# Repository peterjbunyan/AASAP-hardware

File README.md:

# AASAP-hardware
KiCAD Schematics, PCBs and Gerbers for the AASAP computer's hardware.

The AASAP (Almost As Simple As Possible) computer is loosely based on the [8 bit breadboard computer](https://eater.net/8bit) built by Ben Eater which is turn was based on the SAP-1 (Simple As Possible - 1) design. The design of this computer builds on the knowledge from [Ben Eater's YouTube videos](https://www.youtube.com/playlist?list=PLowKtXNTBypGqImE405J2565dvjafglHU) but does not directly copy the design, and differs in a number of areas, the key ones being:

- Moving to a 16 bit address system for the internal RAM and the Program Counter.
- 32KB of RAM for program and data storage.
- 22 Control Bits to control input, output and special functions for each modules.
- A Wait line to halt the clock while waiting for external input.
- A Program line to disable the output of the control bits, allowing for external manual or automated writing of program data to RAM.
- Output to a 16x4 Character LCD.
- A modular PCB design based on individual cards that are linked together on a backplane PCB.

Here you can see the almost complete AASAP running the following code to count down from 4 to zero:

    start:
      LDI 4     ; Load the A Register with an immediate value (4)
    loop:
      SUI 1     ; Subtract the immediate value (1) from the A Register
      JNZ loop  ; If the result was not zero, jump to loop
      JMP       ; Jump to start

The board connected at the top of the image is a bootloader based on an Arduino Nano. It can write to and read from RAM, and provides a clock for the AASAP.

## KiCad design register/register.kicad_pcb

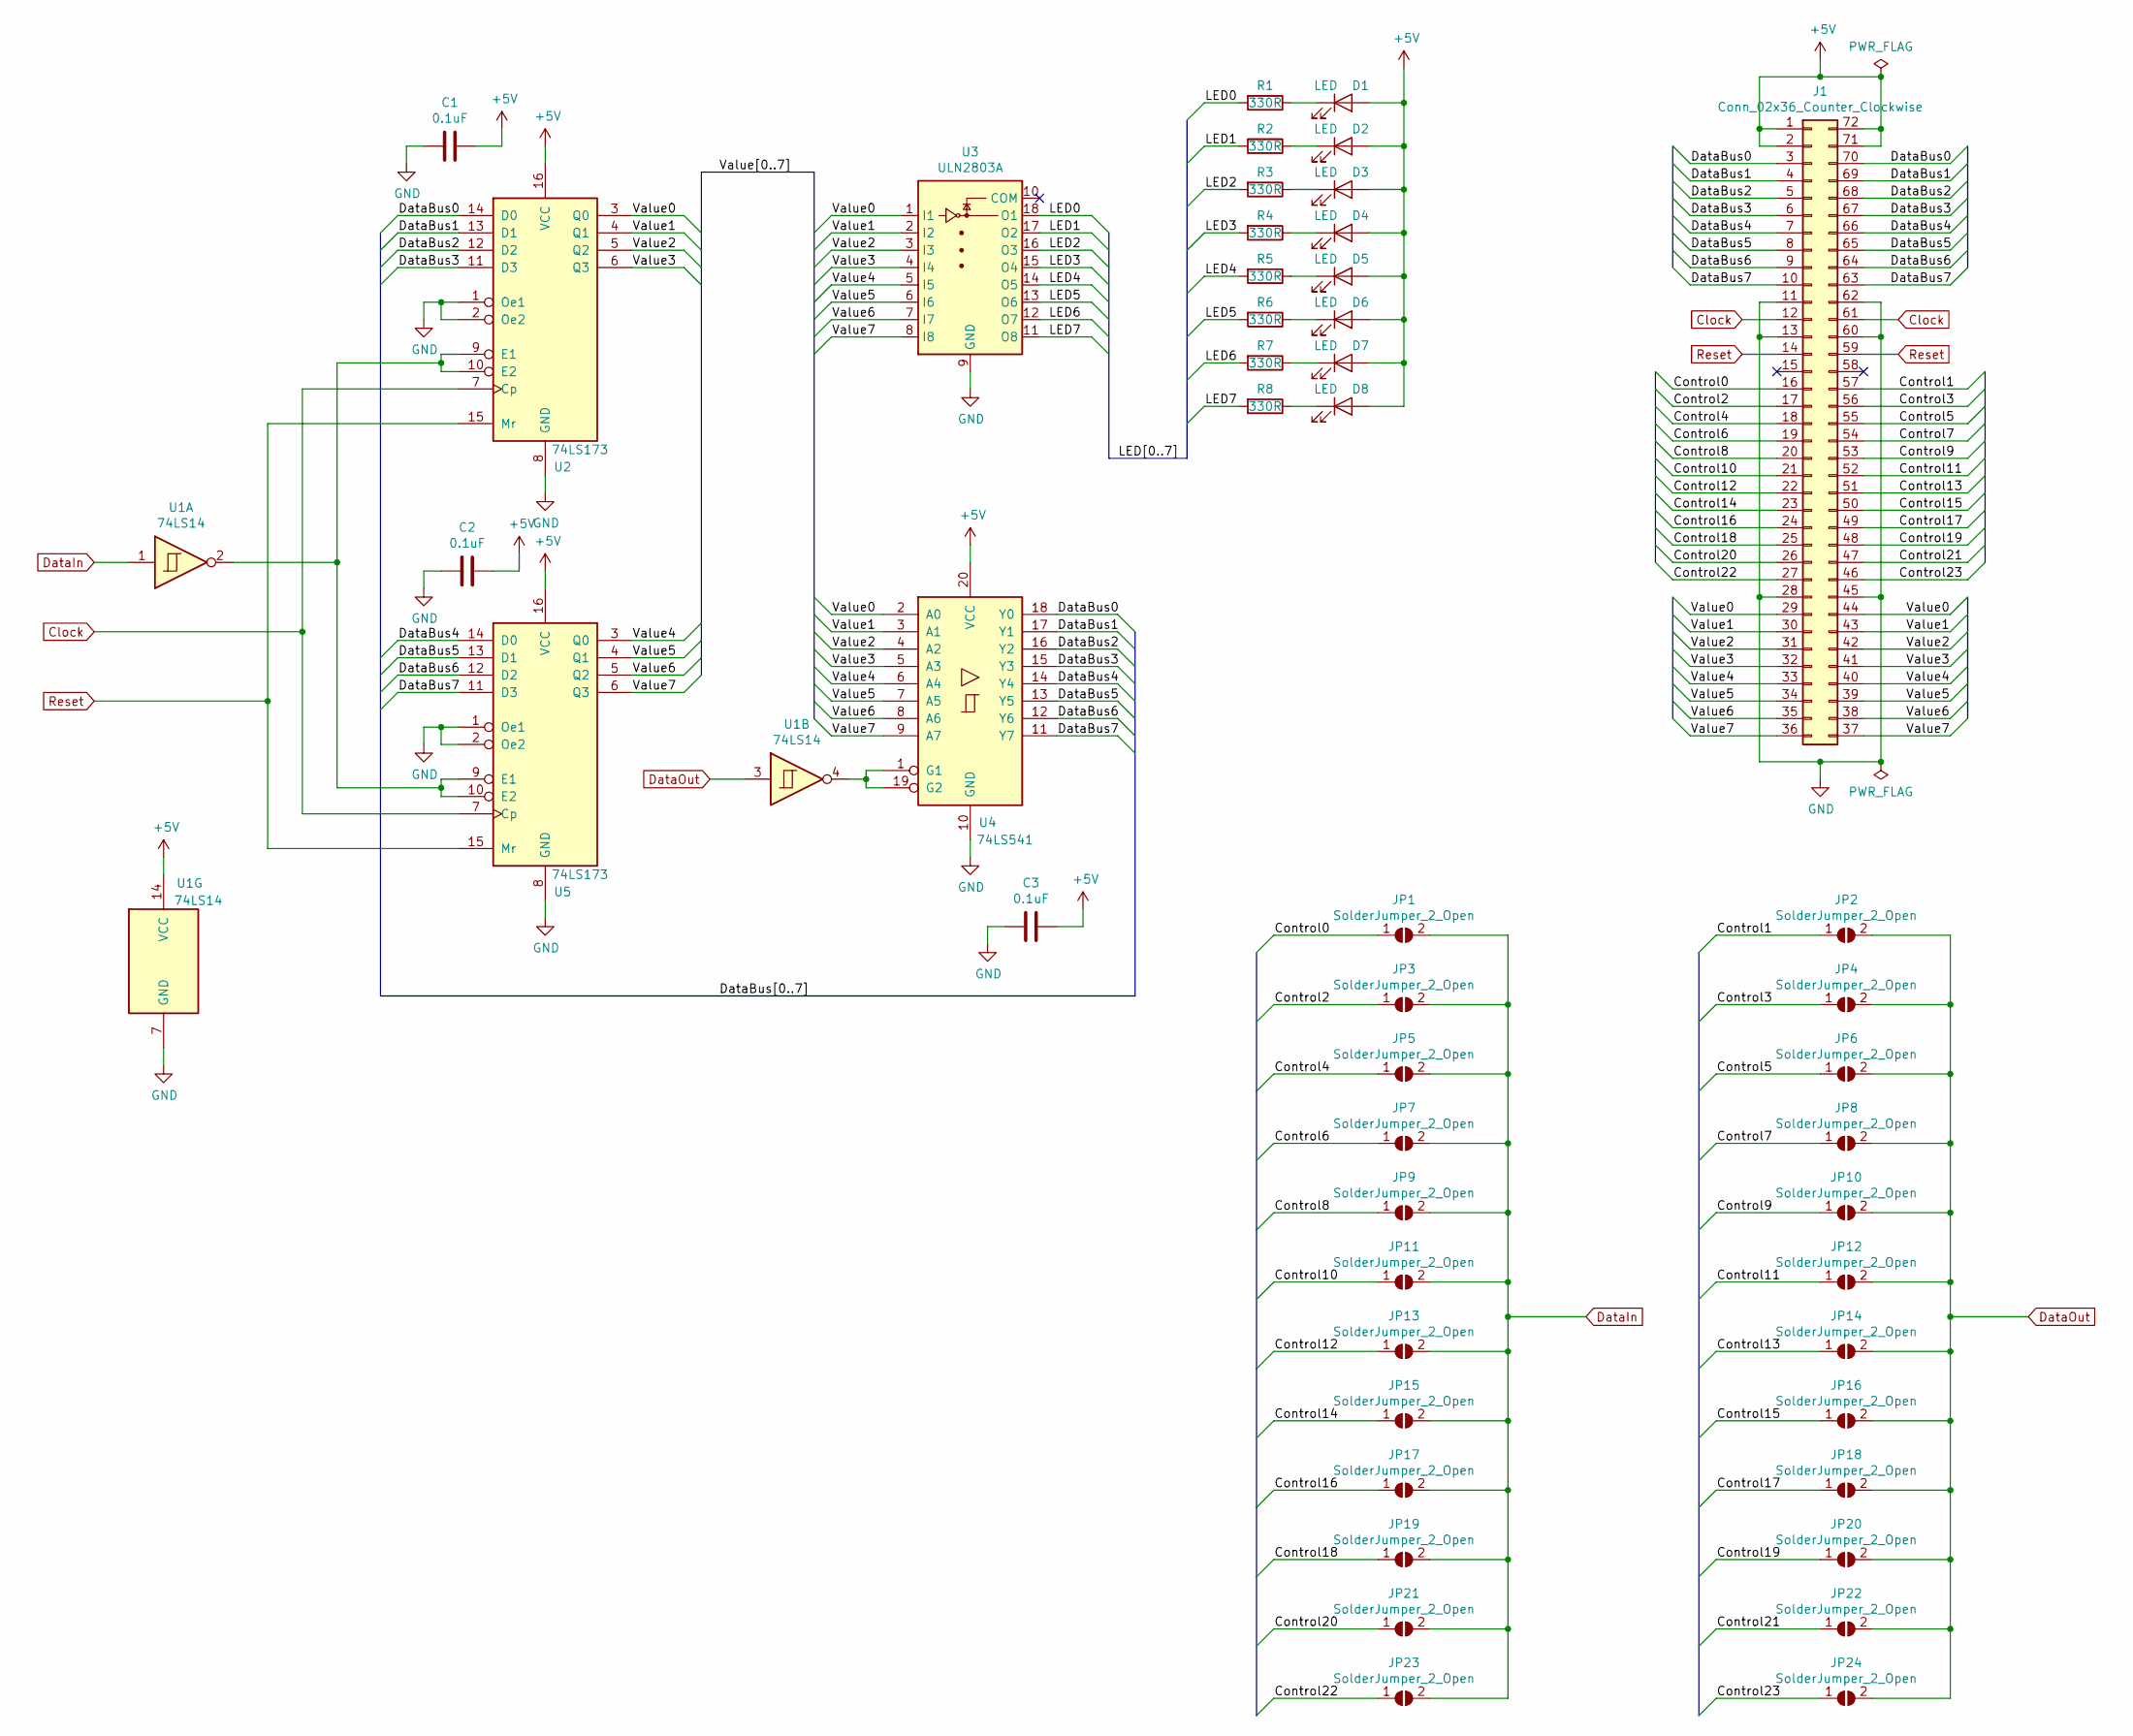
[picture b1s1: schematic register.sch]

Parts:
C1, C2, C3: 0.1uF; C_Disc_D6.0mm_W2.5mm_P5.00mm
D1, D2, D3, D4, D5, D6, D7, D8: LED; LED_D5.0mm_Horizontal_O1.27mm_Z3.0mm
J1: Conn_02x36_Counter_Clockwise; Standard_Edge_II_72_POS_PCB
JP1, JP2, JP3, JP4, JP5, JP6, JP7, JP8, JP9, JP10, JP11, JP12, JP13, JP14, JP15, JP16, JP17, JP18, JP19, JP20, JP21, JP22, JP23, JP24: SolderJumper_2_Open; SolderJumper-2_P1.3mm_Open_TrianglePad1.0x1.5mm
R1, R2, R3, R4, R5, R6, R7, R8: 330R; R_Axial_DIN0204_L3.6mm_D1.6mm_P7.62mm_Horizontal
U1: 74LS14; DIP-14_W7.62mm_Socket
U2, U5: 74LS173; DIP-16_W7.62mm_Socket
U3: ULN2803A; DIP-18_W7.62mm_Socket
U4: 74LS541; DIP-20_W7.62mm_Socket

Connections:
+5V: C1.1, C2.1, C3.1, D1.2 (A), D2.2 (A), D3.2 (A), D4.2 (A), D5.2 (A), D6.2 (A), D7.2 (A), D8.2 (A), J1.1, J1.2, J1.71, J1.72, U1.14 (VCC), U2.16 (VCC), U4.20 (VCC), U5.16 (VCC)
/Control0: J1.16, JP1.1 (A)
/Control1: J1.57, JP2.1 (A)
/Control2: J1.17, JP3.1 (A)
/Control3: J1.56, JP4.1 (A)
/Control4: J1.18, JP5.1 (A)
/Control5: J1.55, JP6.1 (A)
/Control6: J1.19, JP7.1 (A)
/Control7: J1.54, JP8.1 (A)
/Control8: J1.20, JP9.1 (A)
/Control9: J1.53, JP10.1 (A)
/Control10: J1.21, JP11.1 (A)
/Control11: J1.52, JP12.1 (A)
/Control12: J1.22, JP13.1 (A)
/Control13: J1.51, JP14.1 (A)
/Control14: J1.23, JP15.1 (A)
/Control15: J1.50, JP16.1 (A)
/Control16: J1.24, JP17.1 (A)
/Control17: J1.49, JP18.1 (A)
/Control18: J1.25, JP19.1 (A)
/Control19: J1.48, JP20.1 (A)
/Control20: J1.26, JP21.1 (A)
/Control21: J1.47, JP22.1 (A)
/Control22: J1.27, JP23.1 (A)
/Control23: J1.46, JP24.1 (A)
/DataBus0: J1.3, J1.70, U2.14 (D0), U4.18 (Y0)
/DataBus1: J1.4, J1.69, U2.13 (D1), U4.17 (Y1)
/DataBus2: J1.5, J1.68, U2.12 (D2), U4.16 (Y2)
/DataBus3: J1.6, J1.67, U2.11 (D3), U4.15 (Y3)
/DataBus4: J1.7, J1.66, U4.14 (Y4), U5.14 (D0)
/DataBus5: J1.8, J1.65, U4.13 (Y5), U5.13 (D1)
/DataBus6: J1.9, J1.64, U4.12 (Y6), U5.12 (D2)
/DataBus7: J1.10, J1.63, U4.11 (Y7), U5.11 (D3)
/LED0: R1.2, U3.18 (O1)
/LED1: R2.2, U3.17 (O2)
/LED2: R3.2, U3.16 (O3)
/LED3: R4.2, U3.15 (O4)
/LED4: R5.2, U3.14 (O5)
/LED5: R6.2, U3.13 (O6)
/LED6: R7.2, U3.12 (O7)
/LED7: R8.2, U3.11 (O8)
/Value0: J1.29, J1.44, U2.3 (Q0), U3.1 (I1), U4.2 (A0)
/Value1: J1.30, J1.43, U2.4 (Q1), U3.2 (I2), U4.3 (A1)
/Value2: J1.31, J1.42, U2.5 (Q2), U3.3 (I3), U4.4 (A2)
/Value3: J1.32, J1.41, U2.6 (Q3), U3.4 (I4), U4.5 (A3)
/Value4: J1.33, J1.40, U3.5 (I5), U4.6 (A4), U5.3 (Q0)
/Value5: J1.34, J1.39, U3.6 (I6), U4.7 (A5), U5.4 (Q1)
/Value6: J1.35, J1.38, U3.7 (I7), U4.8 (A6), U5.5 (Q2)
/Value7: J1.36, J1.37, U3.8 (I8), U4.9 (A7), U5.6 (Q3)
Clock: J1.12, J1.61, U2.7 (Cp), U5.7 (Cp)
DataIn: JP1.2 (B), JP3.2 (B), JP5.2 (B), JP7.2 (B), JP9.2 (B), JP11.2 (B), JP13.2 (B), JP15.2 (B), JP17.2 (B), JP19.2 (B), JP21.2 (B), JP23.2 (B), U1.1
DataOut: JP2.2 (B), JP4.2 (B), JP6.2 (B), JP8.2 (B), JP10.2 (B), JP12.2 (B), JP14.2 (B), JP16.2 (B), JP18.2 (B), JP20.2 (B), JP22.2 (B), JP24.2 (B), U1.3
GND: C1.2, C2.2, C3.2, J1.11, J1.13, J1.28, J1.45, J1.60, J1.62, U1.7 (GND), U2.1 (Oe1), U2.2 (Oe2), U2.8 (GND), U3.9 (GND), U4.10 (GND), U5.1 (Oe1), U5.2 (Oe2), U5.8 (GND)
unnamed: D1.1 (K), R1.1
unnamed: D2.1 (K), R2.1
unnamed: D3.1 (K), R3.1
unnamed: D4.1 (K), R4.1
unnamed: D5.1 (K), R5.1
unnamed: D6.1 (K), R6.1
unnamed: D7.1 (K), R7.1
unnamed: D8.1 (K), R8.1
unnamed: U1.2, U2.9 (E1), U2.10 (E2), U5.9 (E1), U5.10 (E2)
unnamed: U1.4, U4.1 (G1), U4.19 (G2)
Reset: J1.14, J1.59, U2.15 (Mr), U5.15 (Mr)

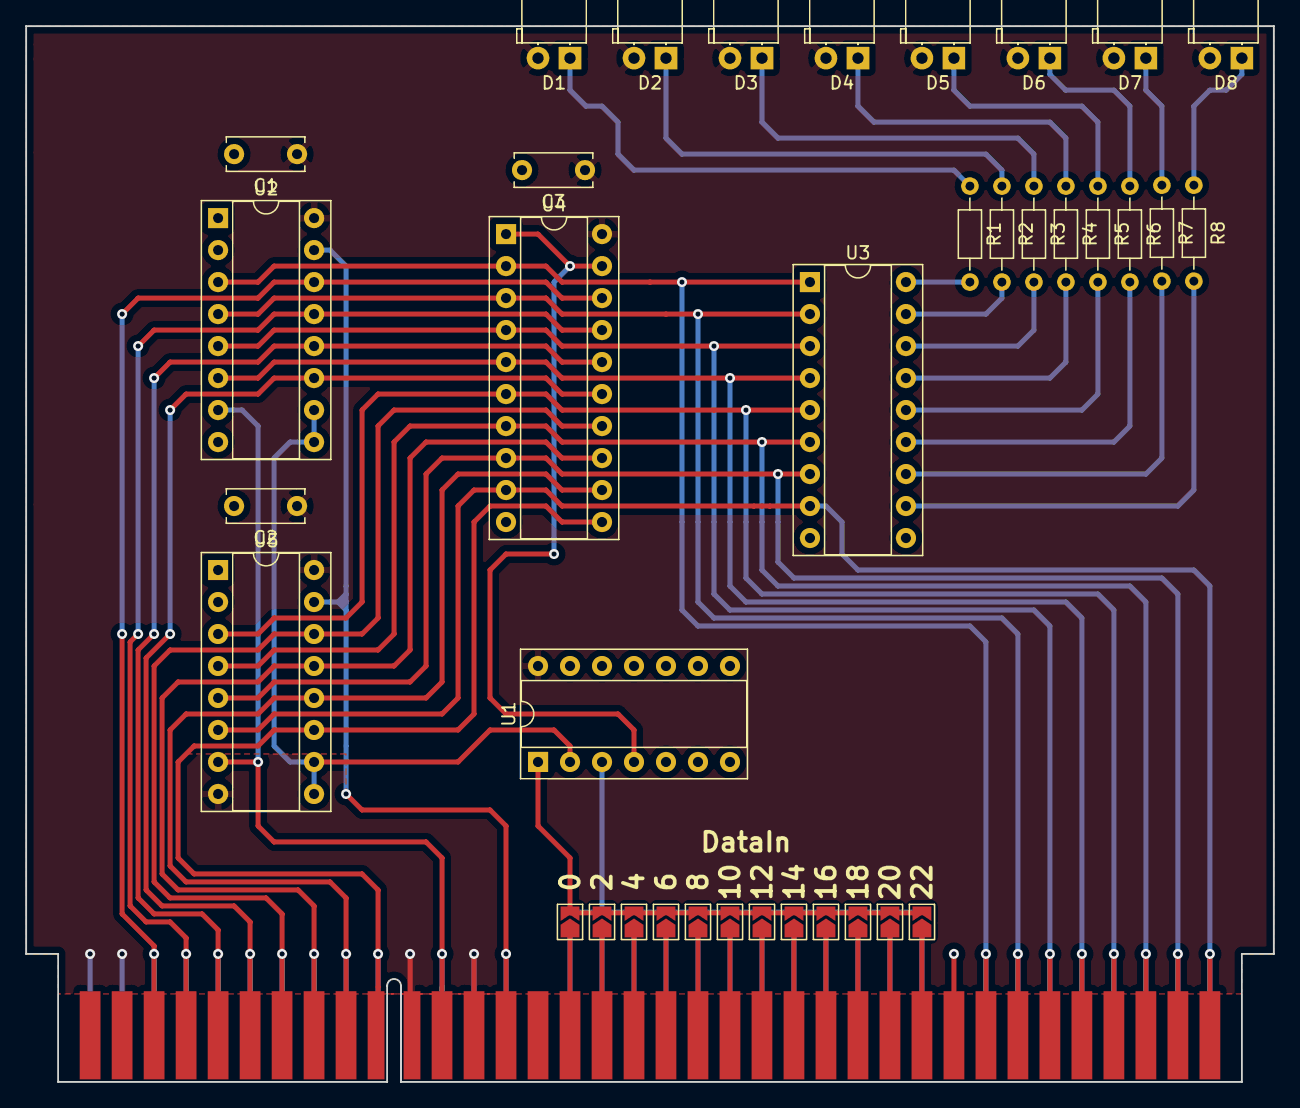
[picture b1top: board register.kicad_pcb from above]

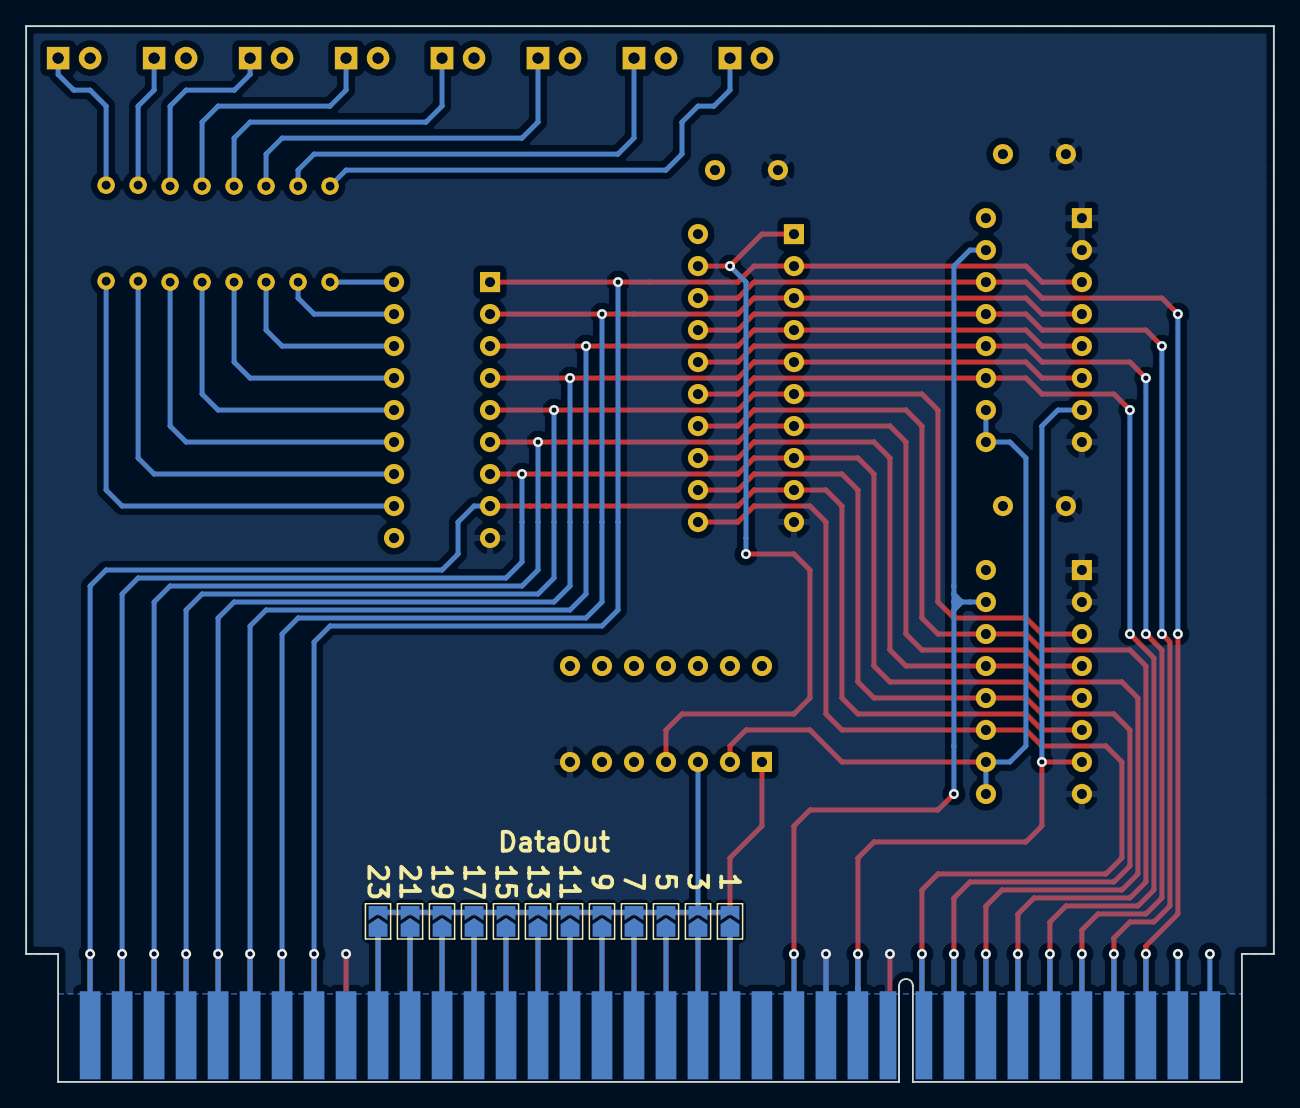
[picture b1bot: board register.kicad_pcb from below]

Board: 2 copper layers, 99.1 x 83.8 mm, 49 parts (12 on the bottom side), 64 nets.

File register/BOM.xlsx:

| Manufacturer | MPN | Description | Value | Quantity | Part references
 | ST Microelectronics | ULN2803A | Darlington Transistor Arrays, DIP18 |  | 1
 | Multicomp Pro | MCL053PD | 5mm Light emitting diode - Red |  | 8
 | Multicomp Pro | 9339418 | 1/4W Through Hole Resistor | 330R | 8
 | Texas Instruments | SN74LS14N | Hex Inverter |  | 1
 | Texas Instruments | SN74LS541N | Buffer |  | 1
 | Texas Instruments | SN74LS173AN | 4-bit D-type Register, 3 state out |  | 2
 | Multicomp Pro | MCFYU6104Z6 | Ceramic Capacitor | 0.1uF | 4
 | Amphenol ICC | DILB20P-223TLF | 20 Pin DIP Socket - 7.62mm |  | 1
 | Amphenol ICC | DILB18P223TLF | 18 Pin DIP Socket - 7.62mm |  | 1
 | Amphenol ICC | DILB16P223TLF | 16 Pin DIP Socket - 7.62mm |  | 2
 | Amphenol ICC | DILB14P-223TLF | 14 Pin DIP Socket - 7.62mm |  | 1

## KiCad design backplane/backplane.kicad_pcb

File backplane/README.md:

# AASAP backplane
This PCB is the backplane that connects all of the computers modules together. It can be chained to other modules using IDC cables, which is necessary to add the number of module required for the computer to function

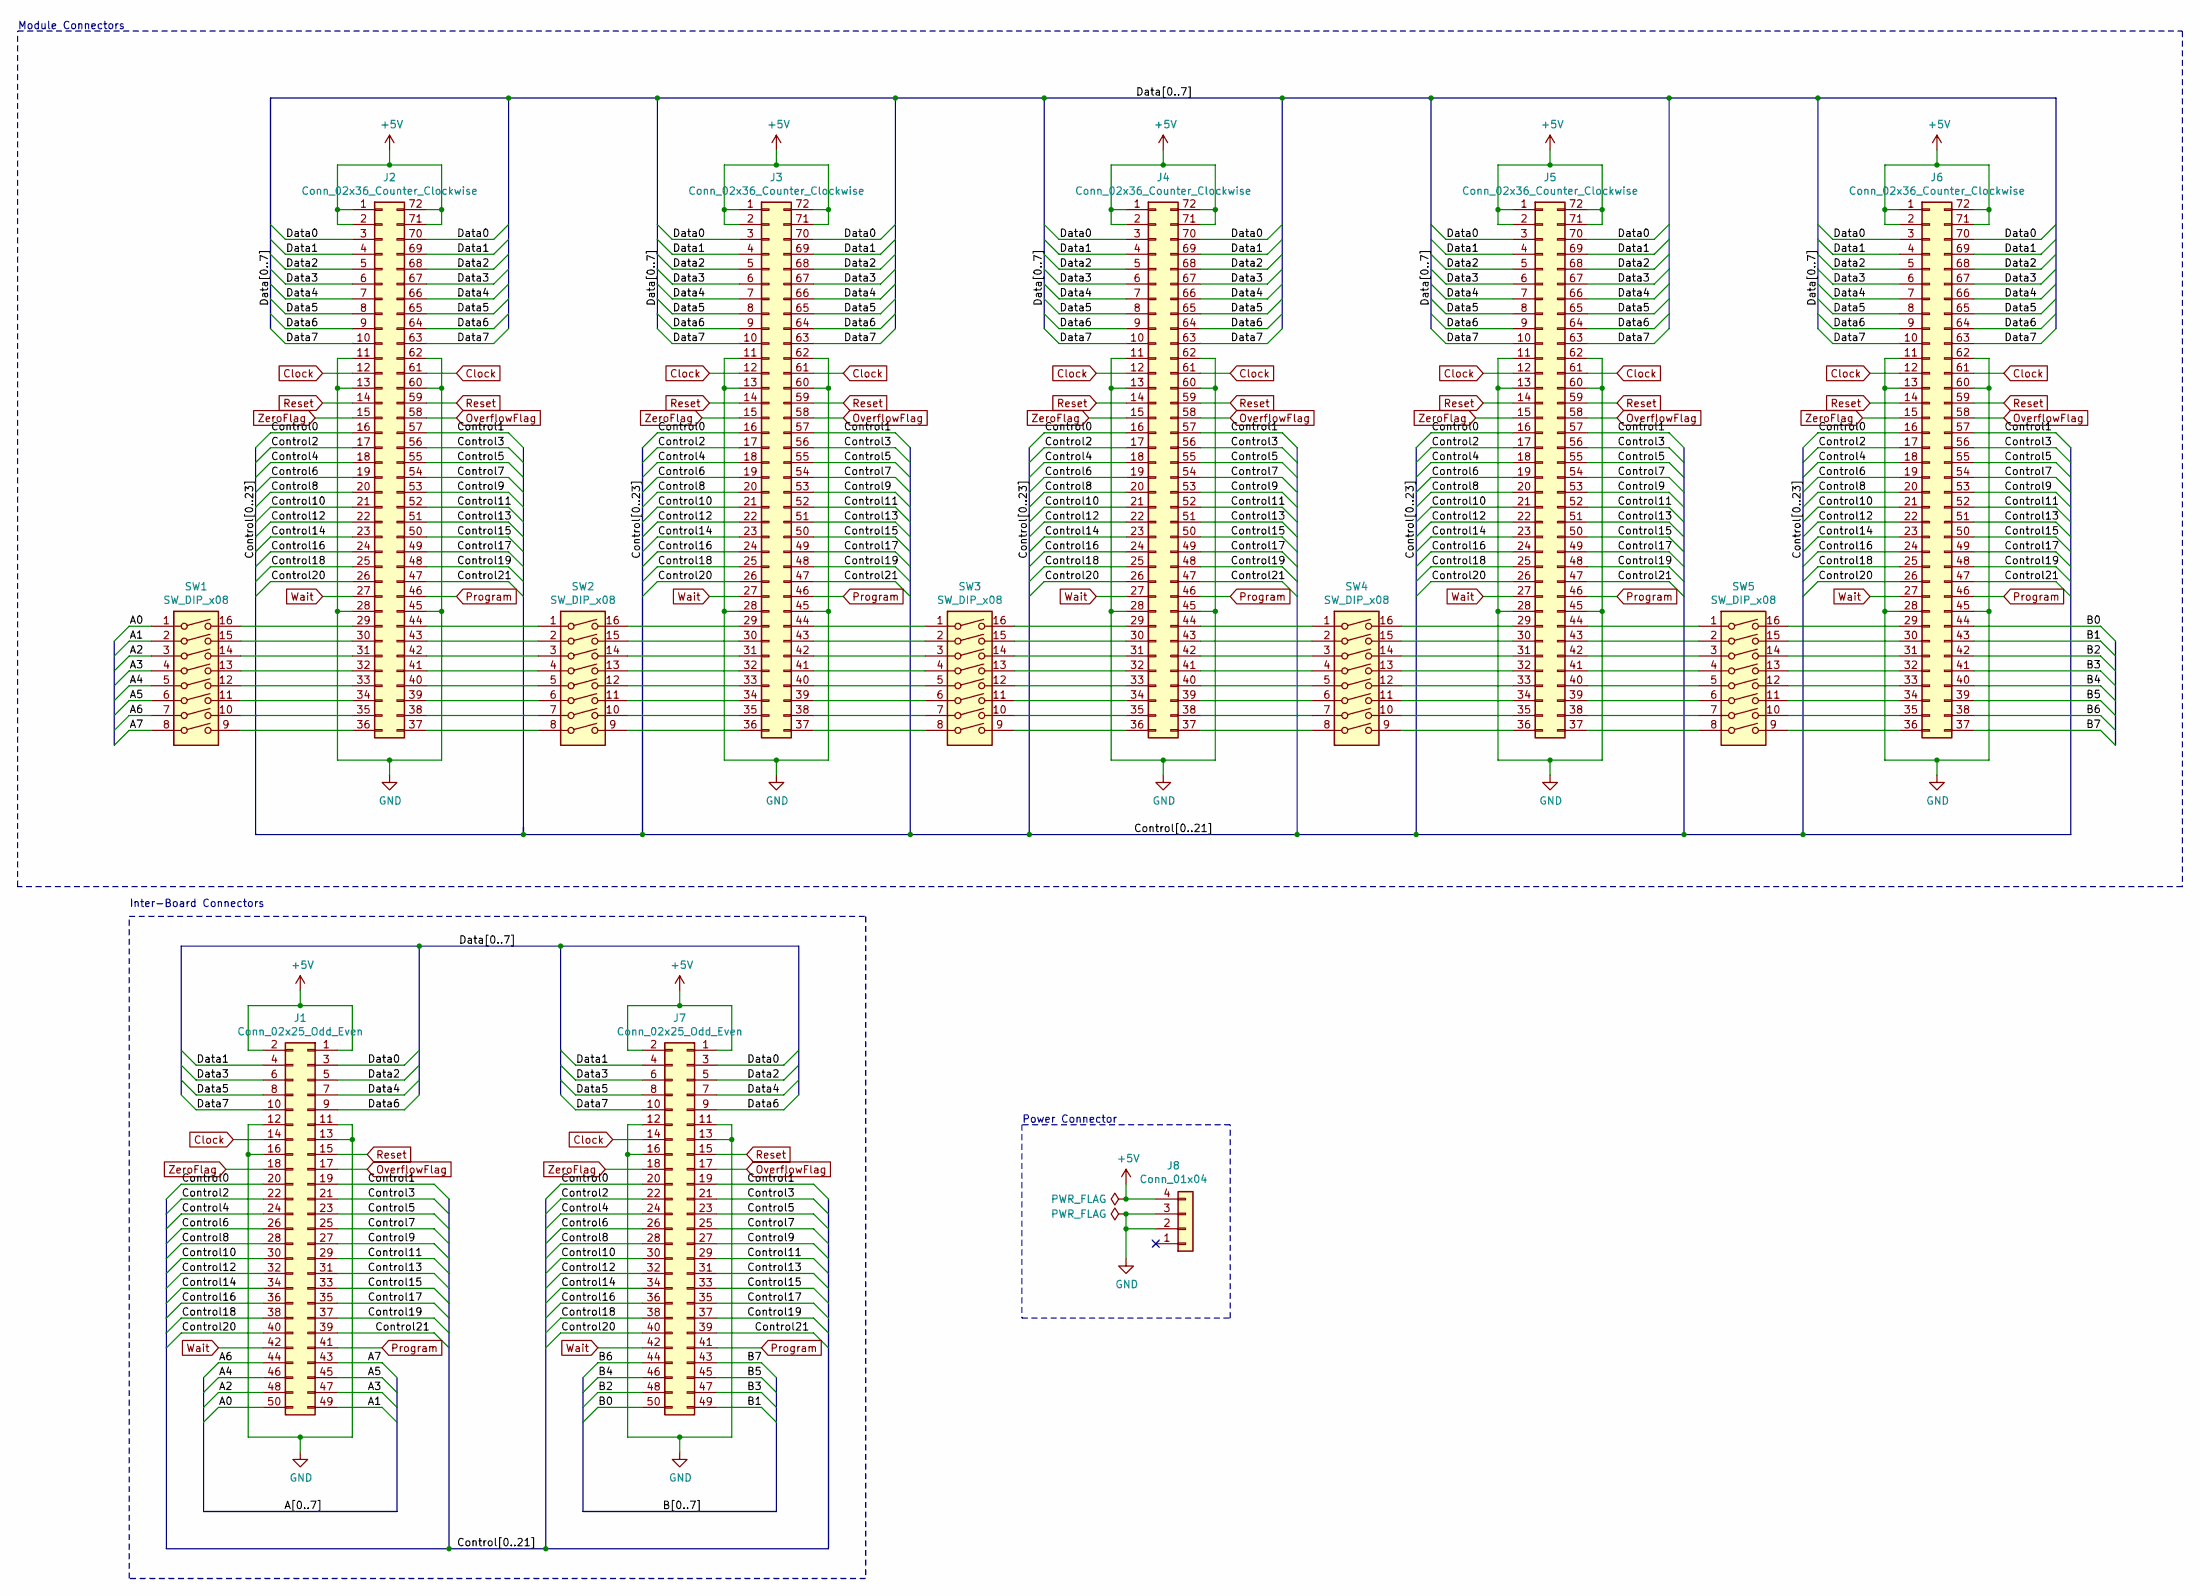
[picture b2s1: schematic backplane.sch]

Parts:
J1, J7: Conn_02x25_Odd_Even; Multicomp_MC9A12-5034_2x25_P2.54mm_Vertical
J2, J3, J4, J5, J6: Conn_02x36_Counter_Clockwise; Standard_Edge_II_72_POS
J8: Conn_01x04; TerminalBlock_bornier-4_P5.08mm
SW1, SW2, SW3, SW4, SW5: SW_DIP_x08; SW_DIP_SPSTx08_Slide_9.78x22.5mm_W7.62mm_P2.54mm

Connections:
+5V: J1.1, J1.2, J2.1, J2.2, J2.71, J2.72, J3.1, J3.2, J3.71, J3.72, J4.1, J4.2, J4.71, J4.72, J5.1, J5.2, J5.71, J5.72, J6.1, J6.2, J6.71, J6.72, J7.1, J7.2, J8.4
/A0: J1.50, SW1.1
/A1: J1.49, SW1.2
/A2: J1.48, SW1.3
/A3: J1.47, SW1.4
/A4: J1.46, SW1.5
/A5: J1.45, SW1.6
/A6: J1.44, SW1.7
/A7: J1.43, SW1.8
/B0: J6.44, J7.50
/B1: J6.43, J7.49
/B2: J6.42, J7.48
/B3: J6.41, J7.47
/B4: J6.40, J7.46
/B5: J6.39, J7.45
/B6: J6.38, J7.44
/B7: J6.37, J7.43
/Control0: J1.20, J2.16, J3.16, J4.16, J5.16, J6.16, J7.20
/Control1: J1.19, J2.57, J3.57, J4.57, J5.57, J6.57, J7.19
/Control2: J1.22, J2.17, J3.17, J4.17, J5.17, J6.17, J7.22
/Control3: J1.21, J2.56, J3.56, J4.56, J5.56, J6.56, J7.21
/Control4: J1.24, J2.18, J3.18, J4.18, J5.18, J6.18, J7.24
/Control5: J1.23, J2.55, J3.55, J4.55, J5.55, J6.55, J7.23
/Control6: J1.26, J2.19, J3.19, J4.19, J5.19, J6.19, J7.26
/Control7: J1.25, J2.54, J3.54, J4.54, J5.54, J6.54, J7.25
/Control8: J1.28, J2.20, J3.20, J4.20, J5.20, J6.20, J7.28
/Control9: J1.27, J2.53, J3.53, J4.53, J5.53, J6.53, J7.27
/Control10: J1.30, J2.21, J3.21, J4.21, J5.21, J6.21, J7.30
/Control11: J1.29, J2.52, J3.52, J4.52, J5.52, J6.52, J7.29
/Control12: J1.32, J2.22, J3.22, J4.22, J5.22, J6.22, J7.32
/Control13: J1.31, J2.51, J3.51, J4.51, J5.51, J6.51, J7.31
/Control14: J1.34, J2.23, J3.23, J4.23, J5.23, J6.23, J7.34
/Control15: J1.33, J2.50, J3.50, J4.50, J5.50, J6.50, J7.33
/Control16: J1.36, J2.24, J3.24, J4.24, J5.24, J6.24, J7.36
/Control17: J1.35, J2.49, J3.49, J4.49, J5.49, J6.49, J7.35
/Control18: J1.38, J2.25, J3.25, J4.25, J5.25, J6.25, J7.38
/Control19: J1.37, J2.48, J3.48, J4.48, J5.48, J6.48, J7.37
/Control20: J1.40, J2.26, J3.26, J4.26, J5.26, J6.26, J7.40
/Control21: J1.39, J2.47, J3.47, J4.47, J5.47, J6.47, J7.39
/Data0: J1.3, J2.3, J2.70, J3.3, J3.70, J4.3, J4.70, J5.3, J5.70, J6.3, J6.70, J7.3
/Data1: J1.4, J2.4, J2.69, J3.4, J3.69, J4.4, J4.69, J5.4, J5.69, J6.4, J6.69, J7.4
/Data2: J1.5, J2.5, J2.68, J3.5, J3.68, J4.5, J4.68, J5.5, J5.68, J6.5, J6.68, J7.5
/Data3: J1.6, J2.6, J2.67, J3.6, J3.67, J4.6, J4.67, J5.6, J5.67, J6.6, J6.67, J7.6
/Data4: J1.7, J2.7, J2.66, J3.7, J3.66, J4.7, J4.66, J5.7, J5.66, J6.7, J6.66, J7.7
/Data5: J1.8, J2.8, J2.65, J3.8, J3.65, J4.8, J4.65, J5.8, J5.65, J6.8, J6.65, J7.8
/Data6: J1.9, J2.9, J2.64, J3.9, J3.64, J4.9, J4.64, J5.9, J5.64, J6.9, J6.64, J7.9
/Data7: J1.10, J2.10, J2.63, J3.10, J3.63, J4.10, J4.63, J5.10, J5.63, J6.10, J6.63, J7.10
Clock: J1.14, J2.12, J2.61, J3.12, J3.61, J4.12, J4.61, J5.12, J5.61, J6.12, J6.61, J7.14
GND: J1.11, J1.12, J1.13, J1.16, J2.11, J2.13, J2.28, J2.45, J2.60, J2.62, J3.11, J3.13, J3.28, J3.45, J3.60, J3.62, J4.11, J4.13, J4.28, J4.45, J4.60, J4.62, J5.11, J5.13, J5.28, J5.45, J5.60, J5.62, J6.11, J6.13, J6.28, J6.45, J6.60, J6.62, J7.11, J7.12, J7.13, J7.16, J8.2, J8.3
unnamed: J2.29, SW1.16
unnamed: J2.30, SW1.15
unnamed: J2.31, SW1.14
unnamed: J2.32, SW1.13
unnamed: J2.33, SW1.12
unnamed: J2.34, SW1.11
unnamed: J2.35, SW1.10
unnamed: J2.36, SW1.9
unnamed: J2.37, SW2.8
unnamed: J2.38, SW2.7
unnamed: J2.39, SW2.6
unnamed: J2.40, SW2.5
unnamed: J2.41, SW2.4
unnamed: J2.42, SW2.3
unnamed: J2.43, SW2.2
unnamed: J2.44, SW2.1
unnamed: J3.29, SW2.16
unnamed: J3.30, SW2.15
unnamed: J3.31, SW2.14
unnamed: J3.32, SW2.13
unnamed: J3.33, SW2.12
unnamed: J3.34, SW2.11
unnamed: J3.35, SW2.10
unnamed: J3.36, SW2.9
unnamed: J3.37, SW3.8
unnamed: J3.38, SW3.7
unnamed: J3.39, SW3.6
unnamed: J3.40, SW3.5
unnamed: J3.41, SW3.4
unnamed: J3.42, SW3.3
unnamed: J3.43, SW3.2
unnamed: J3.44, SW3.1
unnamed: J4.29, SW3.16
unnamed: J4.30, SW3.15
unnamed: J4.31, SW3.14
unnamed: J4.32, SW3.13
unnamed: J4.33, SW3.12
unnamed: J4.34, SW3.11
unnamed: J4.35, SW3.10
unnamed: J4.36, SW3.9
unnamed: J4.37, SW4.8
unnamed: J4.38, SW4.7
unnamed: J4.39, SW4.6
unnamed: J4.40, SW4.5
unnamed: J4.41, SW4.4
unnamed: J4.42, SW4.3
unnamed: J4.43, SW4.2
unnamed: J4.44, SW4.1
unnamed: J5.29, SW4.16
unnamed: J5.30, SW4.15
unnamed: J5.31, SW4.14
unnamed: J5.32, SW4.13
unnamed: J5.33, SW4.12
unnamed: J5.34, SW4.11
unnamed: J5.35, SW4.10
unnamed: J5.36, SW4.9
unnamed: J5.37, SW5.8
unnamed: J5.38, SW5.7
unnamed: J5.39, SW5.6
unnamed: J5.40, SW5.5
unnamed: J5.41, SW5.4
unnamed: J5.42, SW5.3
unnamed: J5.43, SW5.2
unnamed: J5.44, SW5.1
unnamed: J6.29, SW5.16
unnamed: J6.30, SW5.15
unnamed: J6.31, SW5.14
unnamed: J6.32, SW5.13
unnamed: J6.33, SW5.12
unnamed: J6.34, SW5.11
unnamed: J6.35, SW5.10
unnamed: J6.36, SW5.9
OverflowFlag: J1.17, J2.58, J3.58, J4.58, J5.58, J6.58, J7.17
Program: J1.41, J2.46, J3.46, J4.46, J5.46, J6.46, J7.41
Reset: J1.15, J2.14, J2.59, J3.14, J3.59, J4.14, J4.59, J5.14, J5.59, J6.14, J6.59, J7.15
Wait: J1.42, J2.27, J3.27, J4.27, J5.27, J6.27, J7.42
ZeroFlag: J1.18, J2.15, J3.15, J4.15, J5.15, J6.15, J7.18

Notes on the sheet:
Inter-Board Connectors
Power Connector
Module Connectors

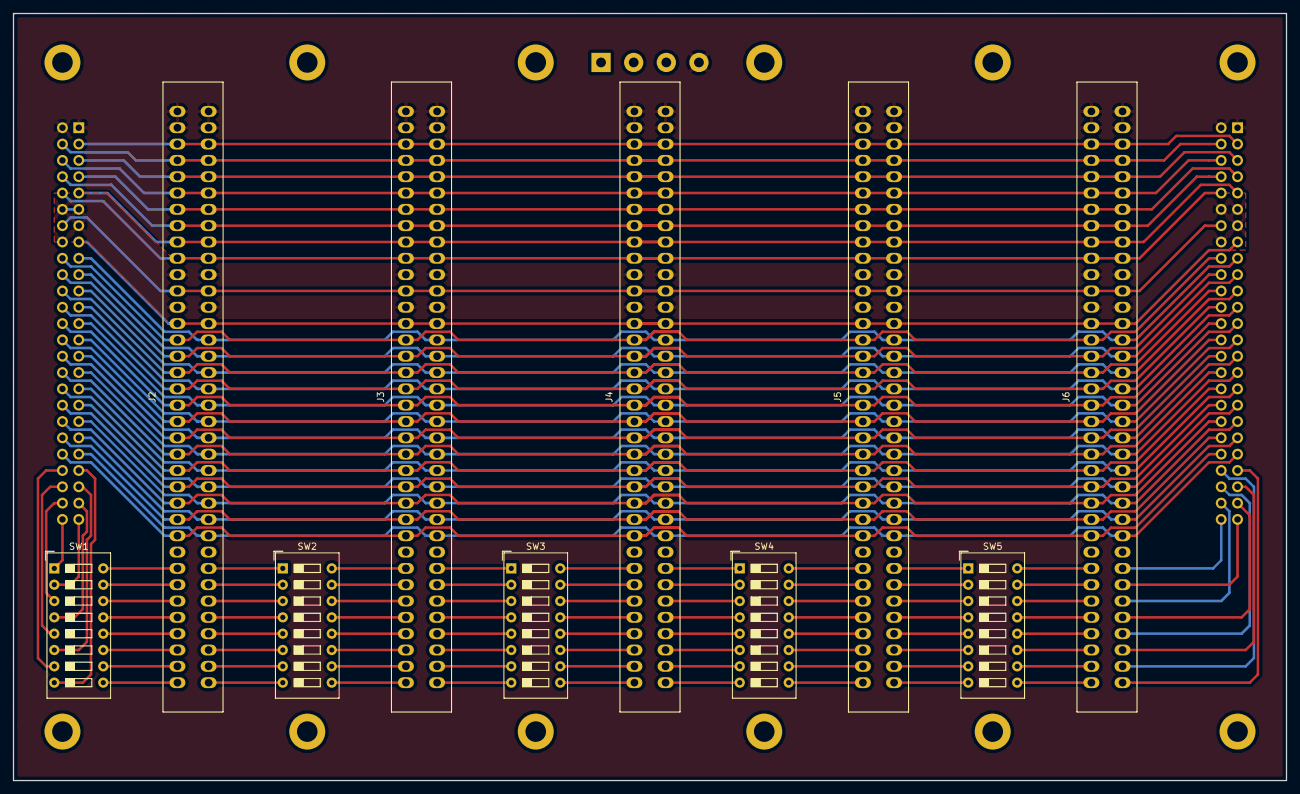
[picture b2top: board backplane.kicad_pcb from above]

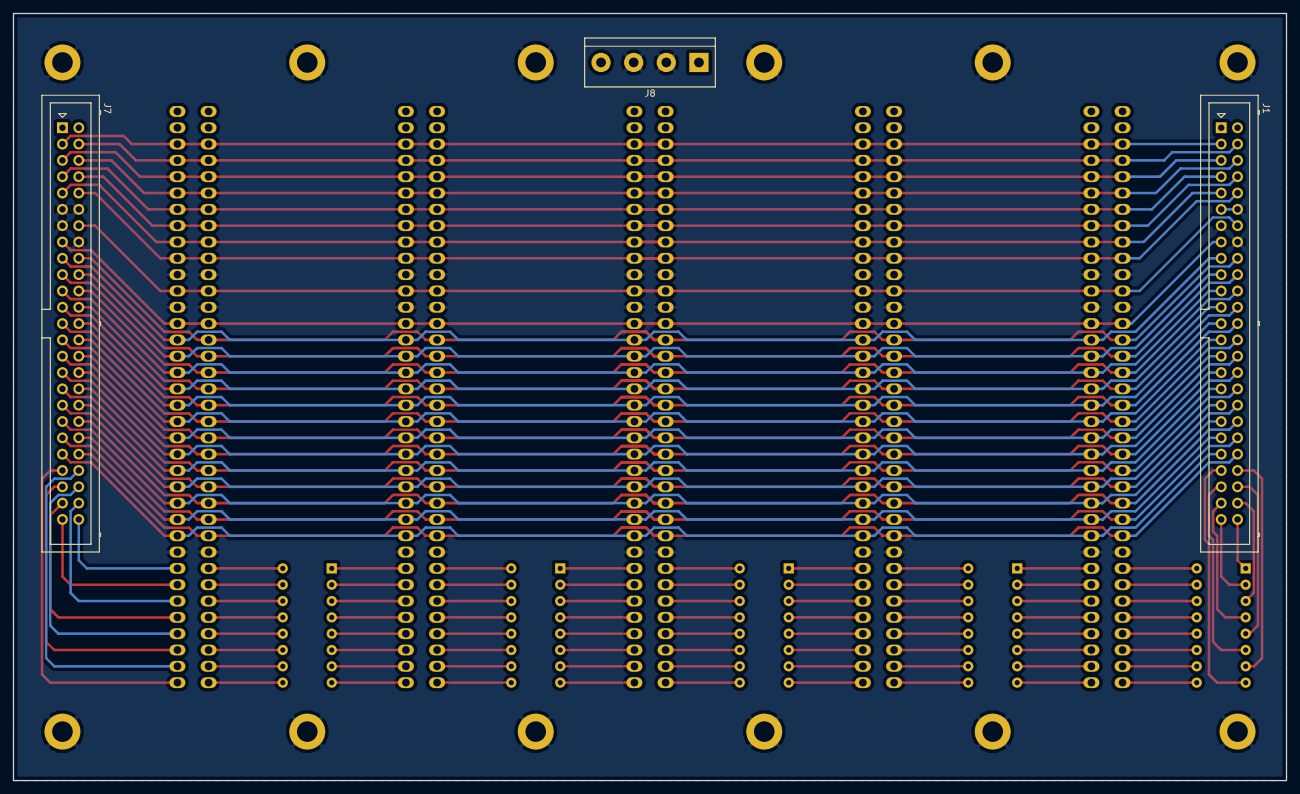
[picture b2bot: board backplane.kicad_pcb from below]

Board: 2 copper layers, 198.1 x 119.4 mm, 13 parts (3 on the bottom side), 126 nets.

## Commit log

2020-05-20 Initial Commit Initial commit with a basic README and files for the computer backplane
2020-06-02 Added BOM for backplane
2020-06-02 Added Register Files
2020-06-02 Added Component References to Register BOM
2020-06-07 Added Counting Animation to README
